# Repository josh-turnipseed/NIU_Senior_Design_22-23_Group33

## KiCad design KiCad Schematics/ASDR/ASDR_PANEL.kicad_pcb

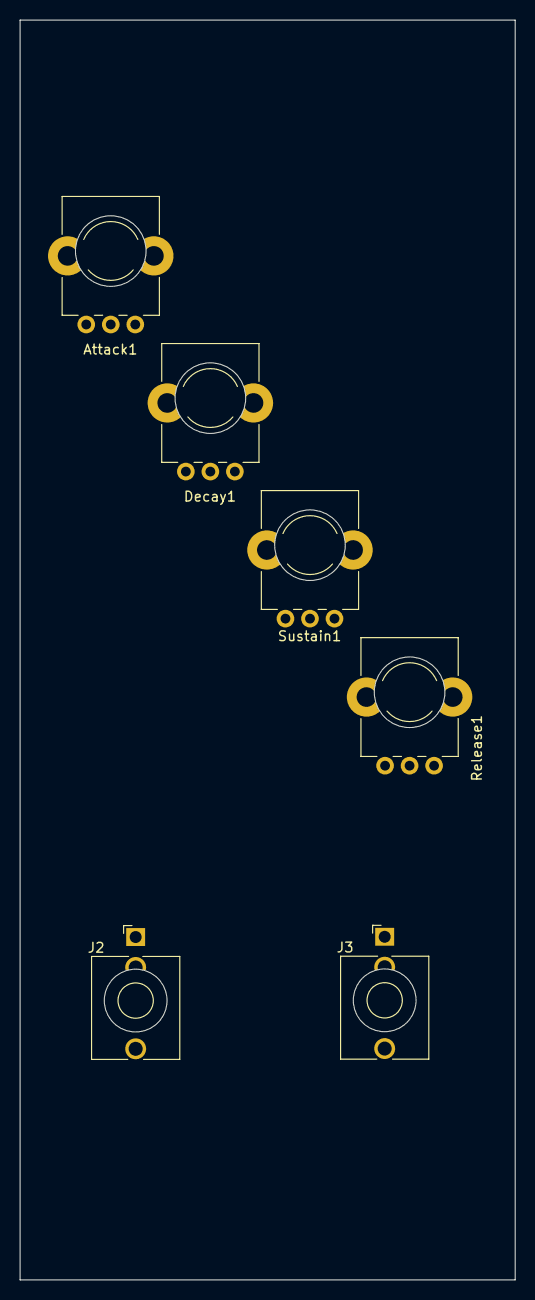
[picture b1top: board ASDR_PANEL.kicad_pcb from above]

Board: 2 copper layers, 50.5 x 128.5 mm, 8 parts (0 on the bottom side), 4 nets, no tracks yet.

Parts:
Attack1: 1M; Alpha_9mm_Potentiometer
Decay1: 500k; Alpha_9mm_Potentiometer
J2: GATE; Jack_3.5mm_QingPu_WQP-PJ398SM_Vertical_CircularHoles
J3: OUT; Jack_3.5mm_QingPu_WQP-PJ398SM_Vertical_CircularHoles
Ref**: Subminiature_Switch; Sub_Miniature_Switch_MountingHole_3.5mm
Ref**#2: Subminiature_Switch; Sub_Miniature_Switch_MountingHole_3.5mm
Release1: 500k; Alpha_9mm_Potentiometer
Sustain1: 500k; Alpha_9mm_Potentiometer

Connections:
GND: J2.S, J2.TN, J3.S
unnamed: Attack1.2, Attack1.3
unnamed: Release1.2, Release1.3
unnamed: Decay1.2, Decay1.3

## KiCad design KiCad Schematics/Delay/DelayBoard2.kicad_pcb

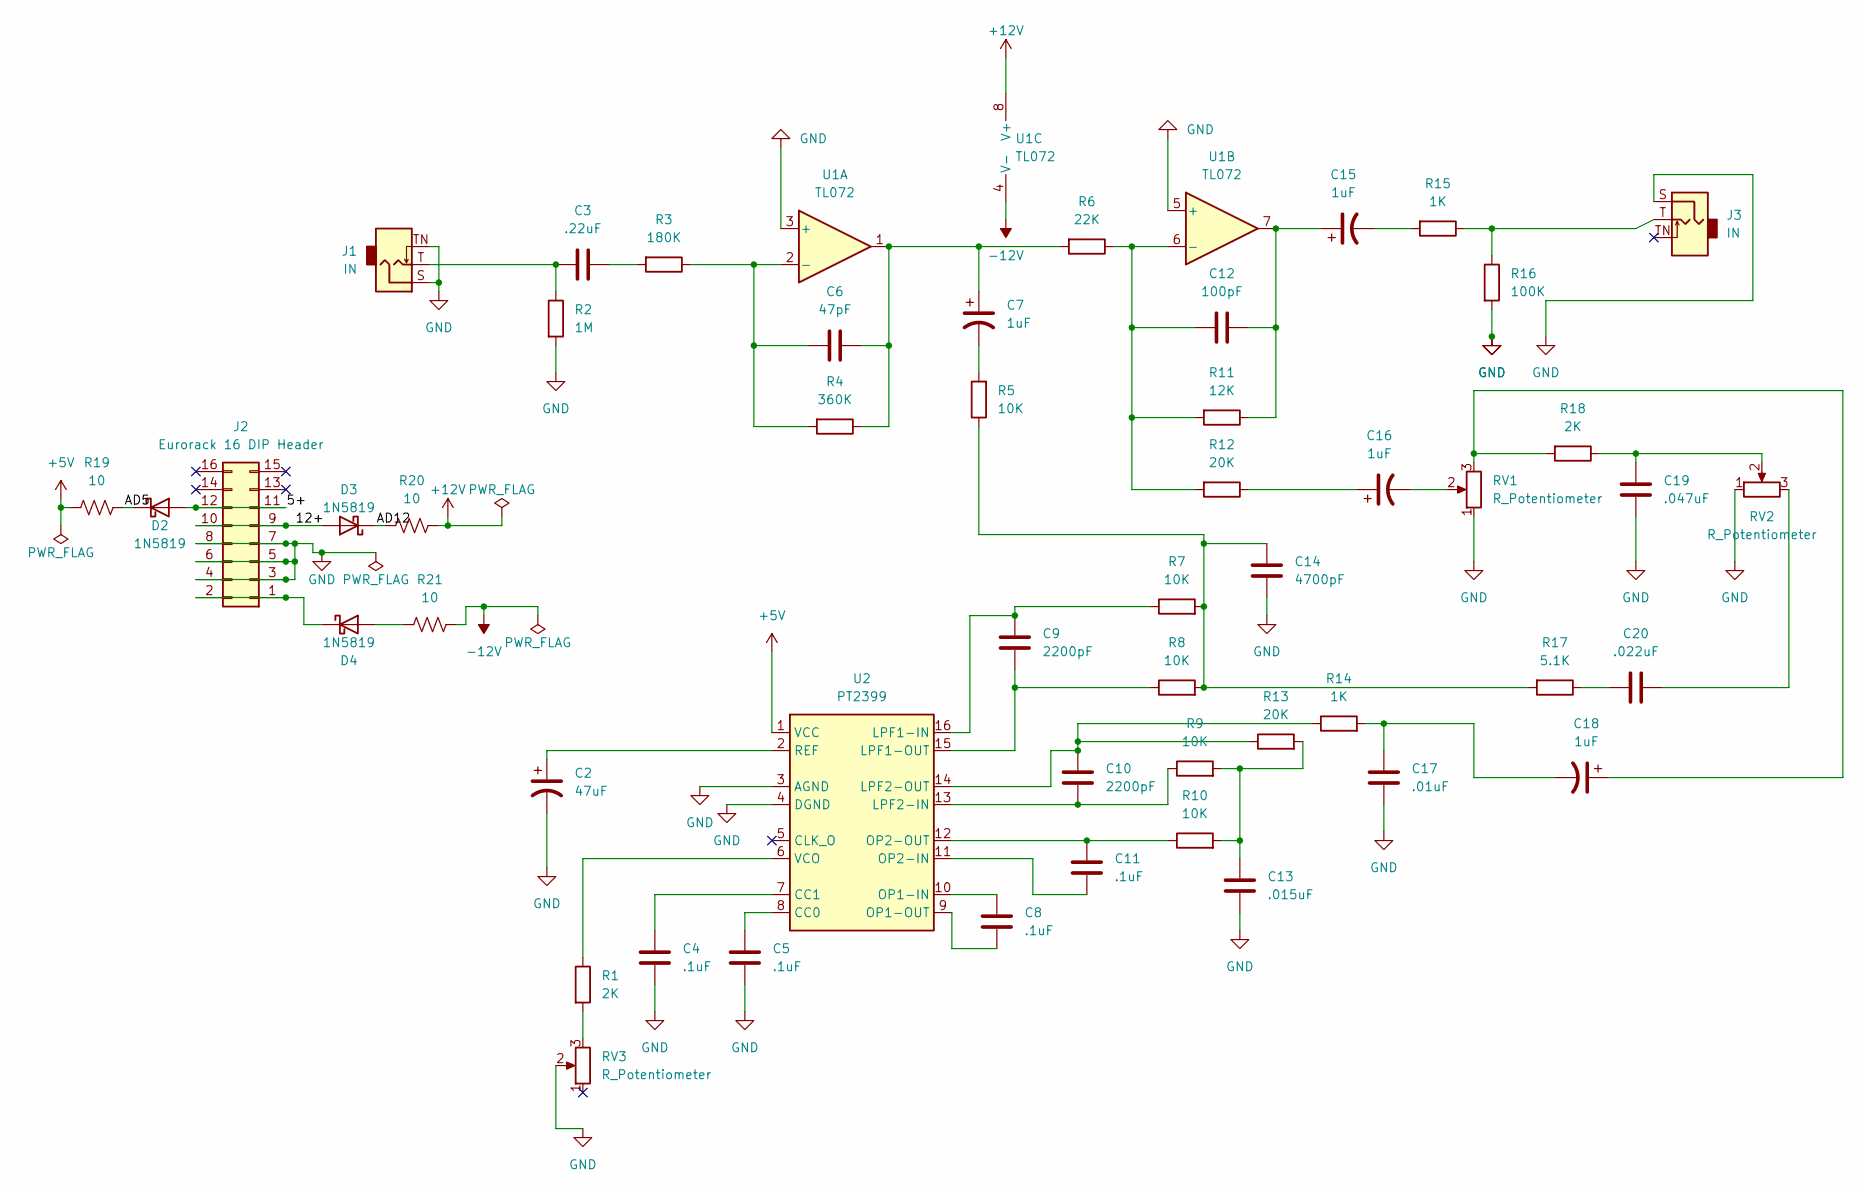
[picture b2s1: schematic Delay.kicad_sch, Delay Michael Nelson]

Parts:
C2: 47uF; CP_Radial_D5.0mm_P2.00mm
C3: .22uF; C_Disc_D3.8mm_W2.6mm_P2.50mm
C4, C5, C8, C11: .1uF; C_Disc_D3.8mm_W2.6mm_P2.50mm
C6: 47pF; C_Disc_D3.8mm_W2.6mm_P2.50mm
C7, C15, C16, C18: 1uF; CP_Radial_D5.0mm_P2.00mm
C9, C10: 2200pF; C_Disc_D3.8mm_W2.6mm_P2.50mm
C12: 100pF; C_Disc_D3.8mm_W2.6mm_P2.50mm
C13: .015uF; C_Disc_D3.8mm_W2.6mm_P2.50mm
C14: 4700pF; C_Disc_D3.8mm_W2.6mm_P2.50mm
C17: .01uF; C_Disc_D3.8mm_W2.6mm_P2.50mm
C19: .047uF; C_Disc_D3.8mm_W2.6mm_P2.50mm
C20: .022uF; C_Disc_D3.8mm_W2.6mm_P2.50mm
D2, D3, D4: 1N5819; D_DO-41_SOD81_P10.16mm_Horizontal
J1, J3: IN; Jack_3.5mm_QingPu_WQP-PJ398SM_Vertical_CircularHoles
J2: Eurorack 16 DIP Header; Eurorack_16_pin_header
R1, R18: 2K; R_Axial_DIN0207_L6.3mm_D2.5mm_P7.62mm_Horizontal
R2: 1M; R_Axial_DIN0207_L6.3mm_D2.5mm_P7.62mm_Horizontal
R3: 180K; R_Axial_DIN0207_L6.3mm_D2.5mm_P7.62mm_Horizontal
R4: 360K; R_Axial_DIN0207_L6.3mm_D2.5mm_P7.62mm_Horizontal
R5, R7, R8, R9, R10: 10K; R_Axial_DIN0207_L6.3mm_D2.5mm_P7.62mm_Horizontal
R6: 22K; R_Axial_DIN0207_L6.3mm_D2.5mm_P7.62mm_Horizontal
R11: 12K; R_Axial_DIN0207_L6.3mm_D2.5mm_P7.62mm_Horizontal
R12, R13: 20K; R_Axial_DIN0207_L6.3mm_D2.5mm_P7.62mm_Horizontal
R14, R15: 1K; R_Axial_DIN0207_L6.3mm_D2.5mm_P7.62mm_Horizontal
R16: 100K; R_Axial_DIN0207_L6.3mm_D2.5mm_P7.62mm_Horizontal
R17: 5.1K; R_Axial_DIN0207_L6.3mm_D2.5mm_P7.62mm_Horizontal
R19, R20, R21: 10; R_Axial_DIN0207_L6.3mm_D2.5mm_P7.62mm_Horizontal
RV1, RV2, RV3: R_Potentiometer; Alpha_9mm_Potentiometer
U1: TL072; DIP-8_W7.62mm
U2: PT2399; DIP-16_W7.62mm

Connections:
+5V: R19.2, U2.1 (VCC)
+12V: R20.1, U1.8 (V+)
-12V: R21.1, U1.4 (V-)
/5+: D2.2 (A), J2.11, J2.12
/12+: D3.2 (A), J2.9, J2.10
/AD5: D2.1 (K), R19.1
/AD12: D3.1 (K), R20.2
GND: C2.2, C4.2, C5.2, C13.2, C14.2, C17.2, C19.1, J1.S, J1.TN, J2.3, J2.4, J2.5, J2.6, J2.7, J2.8, J3.S, R2.2, R16.2, RV1.1, RV2.1, RV3.2, U1.3 (+), U1.5 (+), U2.3 (AGND), U2.4 (DGND)
unnamed: C2.1, U2.2 (REF)
unnamed: C3.1, J1.T, R2.1
unnamed: C3.2, R3.2
unnamed: C4.1, U2.7 (CC1)
unnamed: C5.1, U2.8 (CC0)
unnamed: C6.1, R3.1, R4.2, U1.2 (-)
unnamed: C6.2, C7.1, R4.1, R6.2, U1.1
unnamed: C7.2, R5.2
unnamed: C8.1, U2.10 (OP1-IN)
unnamed: C8.2, U2.9 (OP1-OUT)
unnamed: C9.1, R7.1, U2.16 (LPF1-IN)
unnamed: C9.2, R8.1, U2.15 (LPF1-OUT)
unnamed: C10.1, R13.1, R14.1, U2.14 (LPF2-OUT)
unnamed: C10.2, R9.1, U2.13 (LPF2-IN)
unnamed: C11.1, R10.1, U2.12 (OP2-OUT)
unnamed: C11.2, U2.11 (OP2-IN)
unnamed: C12.1, R6.1, R11.2, R12.2, U1.6 (-)
unnamed: C12.2, C15.1, R11.1, U1.7
unnamed: C13.1, R9.2, R10.2, R13.2
unnamed: C14.1, R5.1, R7.2, R8.2, R17.2
unnamed: C15.2, R15.2
unnamed: C16.1, R12.1
unnamed: C16.2, RV1.2
unnamed: C17.1, C18.2, R14.2
unnamed: C18.1, R18.2, RV1.3
unnamed: C19.2, R18.1, RV2.2
unnamed: C20.1, RV2.3
unnamed: C20.2, R17.1
unnamed: D4.1 (K), J2.1, J2.2
unnamed: D4.2 (A), R21.2
unnamed: J3.T, R15.1, R16.1
unnamed: R1.1, U2.6 (VCO)
unnamed: R1.2, RV3.3

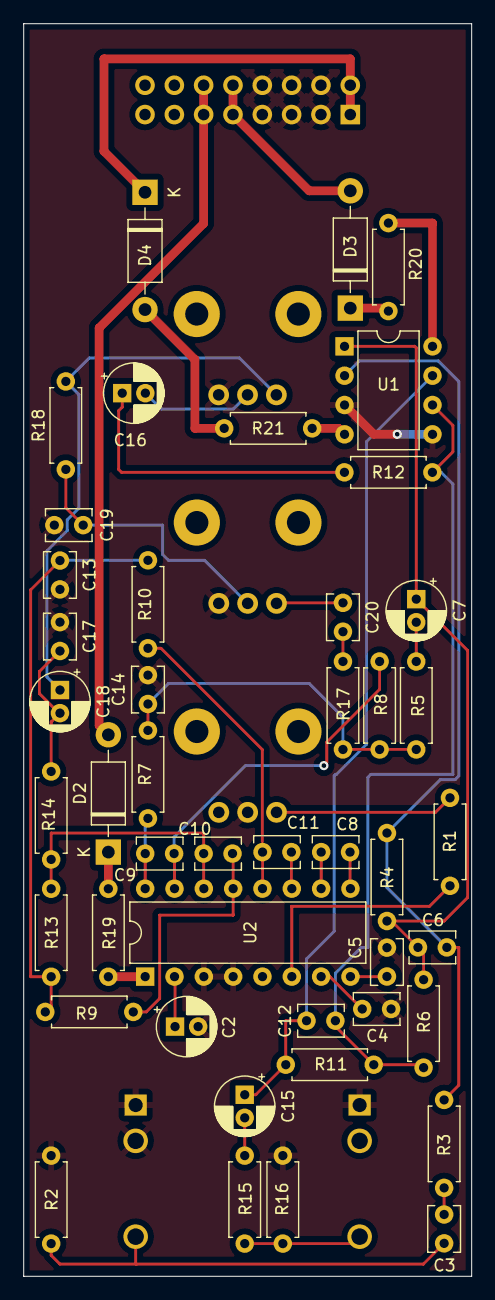
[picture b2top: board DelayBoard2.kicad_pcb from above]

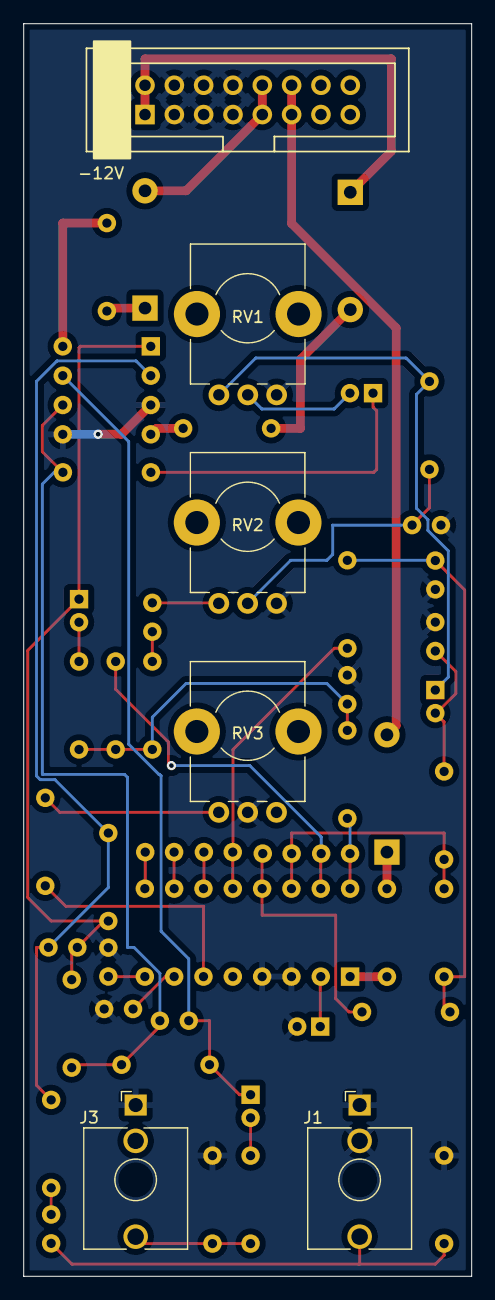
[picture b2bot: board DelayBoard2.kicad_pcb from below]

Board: 2 copper layers, 38.8 x 108.5 mm, 54 parts (6 on the bottom side), 41 nets.

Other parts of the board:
Ref**: Alpha_9mm_pot_hole
Ref**#2, Ref**#3: Subminiature_Switch; Sub_Miniature_Switch_MountingHole_3.5mm

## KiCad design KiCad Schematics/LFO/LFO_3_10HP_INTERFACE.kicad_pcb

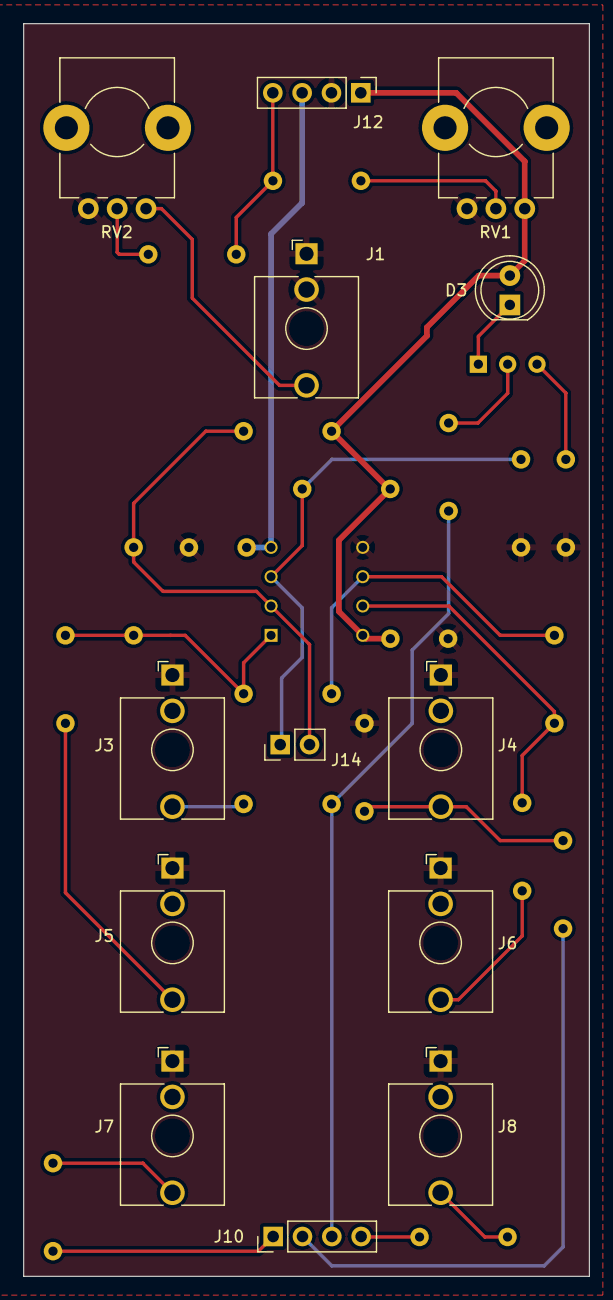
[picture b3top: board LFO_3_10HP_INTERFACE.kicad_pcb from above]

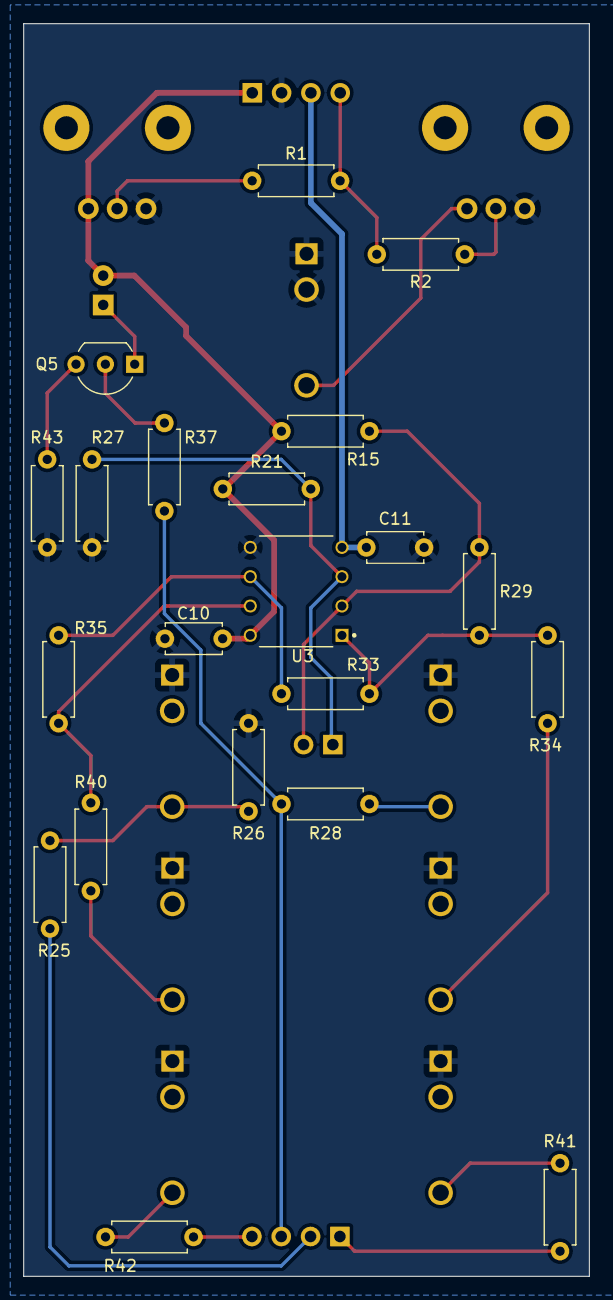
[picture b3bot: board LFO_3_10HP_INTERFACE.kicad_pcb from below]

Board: 2 copper layers, 49.0 x 108.5 mm, 34 parts (21 on the bottom side), 25 nets.

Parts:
C10, C11: 0.1u; C_Disc_D4.7mm_W2.5mm_P5.00mm
D3: LED; LED_D5.0mm
J1: CV IN; Jack_3.5mm_QingPu_WQP-PJ398SM_Vertical_CircularHoles
J3: TRI; Jack_3.5mm_QingPu_WQP-PJ398SM_Vertical_CircularHoles
J4: SQR; Jack_3.5mm_QingPu_WQP-PJ398SM_Vertical_CircularHoles
J5: SINE; Jack_3.5mm_QingPu_WQP-PJ398SM_Vertical_CircularHoles
J6: COSINE; Jack_3.5mm_QingPu_WQP-PJ398SM_Vertical_CircularHoles
J7: RAMP UP; Jack_3.5mm_QingPu_WQP-PJ398SM_Vertical_CircularHoles
J8: RAMP DOWN; Jack_3.5mm_QingPu_WQP-PJ398SM_Vertical_CircularHoles
J10, J12: Conn_01x04; PinHeader_1x04_P2.54mm_Vertical
J14: Conn_01x02; PinHeader_1x02_P2.54mm_Vertical
Q5: BC550; TO-92_Inline_Wide
R1, R2, R25, R26: 100k; R_Axial_DIN0207_L6.3mm_D2.5mm_P7.62mm_Horizontal
R15, R21, R33, R35, R37: 10k; R_Axial_DIN0207_L6.3mm_D2.5mm_P7.62mm_Horizontal
R27, R29: 33k; R_Axial_DIN0207_L6.3mm_D2.5mm_P7.62mm_Horizontal
R28, R34, R40, R41, R42: 1k; R_Axial_DIN0207_L6.3mm_D2.5mm_P7.62mm_Horizontal
R43: 560; R_Axial_DIN0207_L6.3mm_D2.5mm_P7.62mm_Horizontal
RV1, RV2: 100K; Alpha_9mm_Potentiometer_Aligned
U3: TL072CP; DIP794W45P254L959H508Q8

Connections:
+12VA: C10.1, D3.2 (A), J12.1, R15.1, R21.1, RV1.3, U3.8 (V+)
-12VA: C11.1, J12.3, U3.4 (V-)
/CV_Scale: R2.1, RV2.2
GND: C10.2, C11.2, J1.S, J1.TN, J3.S, J4.S, J5.S, J6.S, J7.S, J8.S, J12.2, R26.2, R27.2, R43.2, RV1.1, RV2.1, U3.5 (+)
unnamed: D3.1 (K), Q5.1 (C)
unnamed: J1.T, RV2.3
unnamed: J3.T, R28.1
unnamed: J4.T, R25.1, R26.1
unnamed: J5.T, R34.1
unnamed: J6.T, R40.1
unnamed: J7.T, R41.1
unnamed: J8.T, R42.1
unnamed: Q5.2 (B), R37.1
unnamed: Q5.3 (E), R43.1
unnamed: R1.1, RV1.2
unnamed: R29.2, R33.1, R34.2, U3.1
unnamed: R33.2, R35.1, U3.6 (-)
unnamed: R35.2, R40.2, U3.7
RV2_2: J12.4, R1.2, R2.2
Ramp Down2: J10.4, R42.2
Ramp Up2: J10.1, R41.2
Sqr2: J10.2, R25.2
Tri2: J10.3, R28.2, R37.2
U3_2_2: J14.2, R15.2, R29.1, U3.2 (-)
U3_3_2: J14.1, R21.2, R27.1, U3.3 (+)
